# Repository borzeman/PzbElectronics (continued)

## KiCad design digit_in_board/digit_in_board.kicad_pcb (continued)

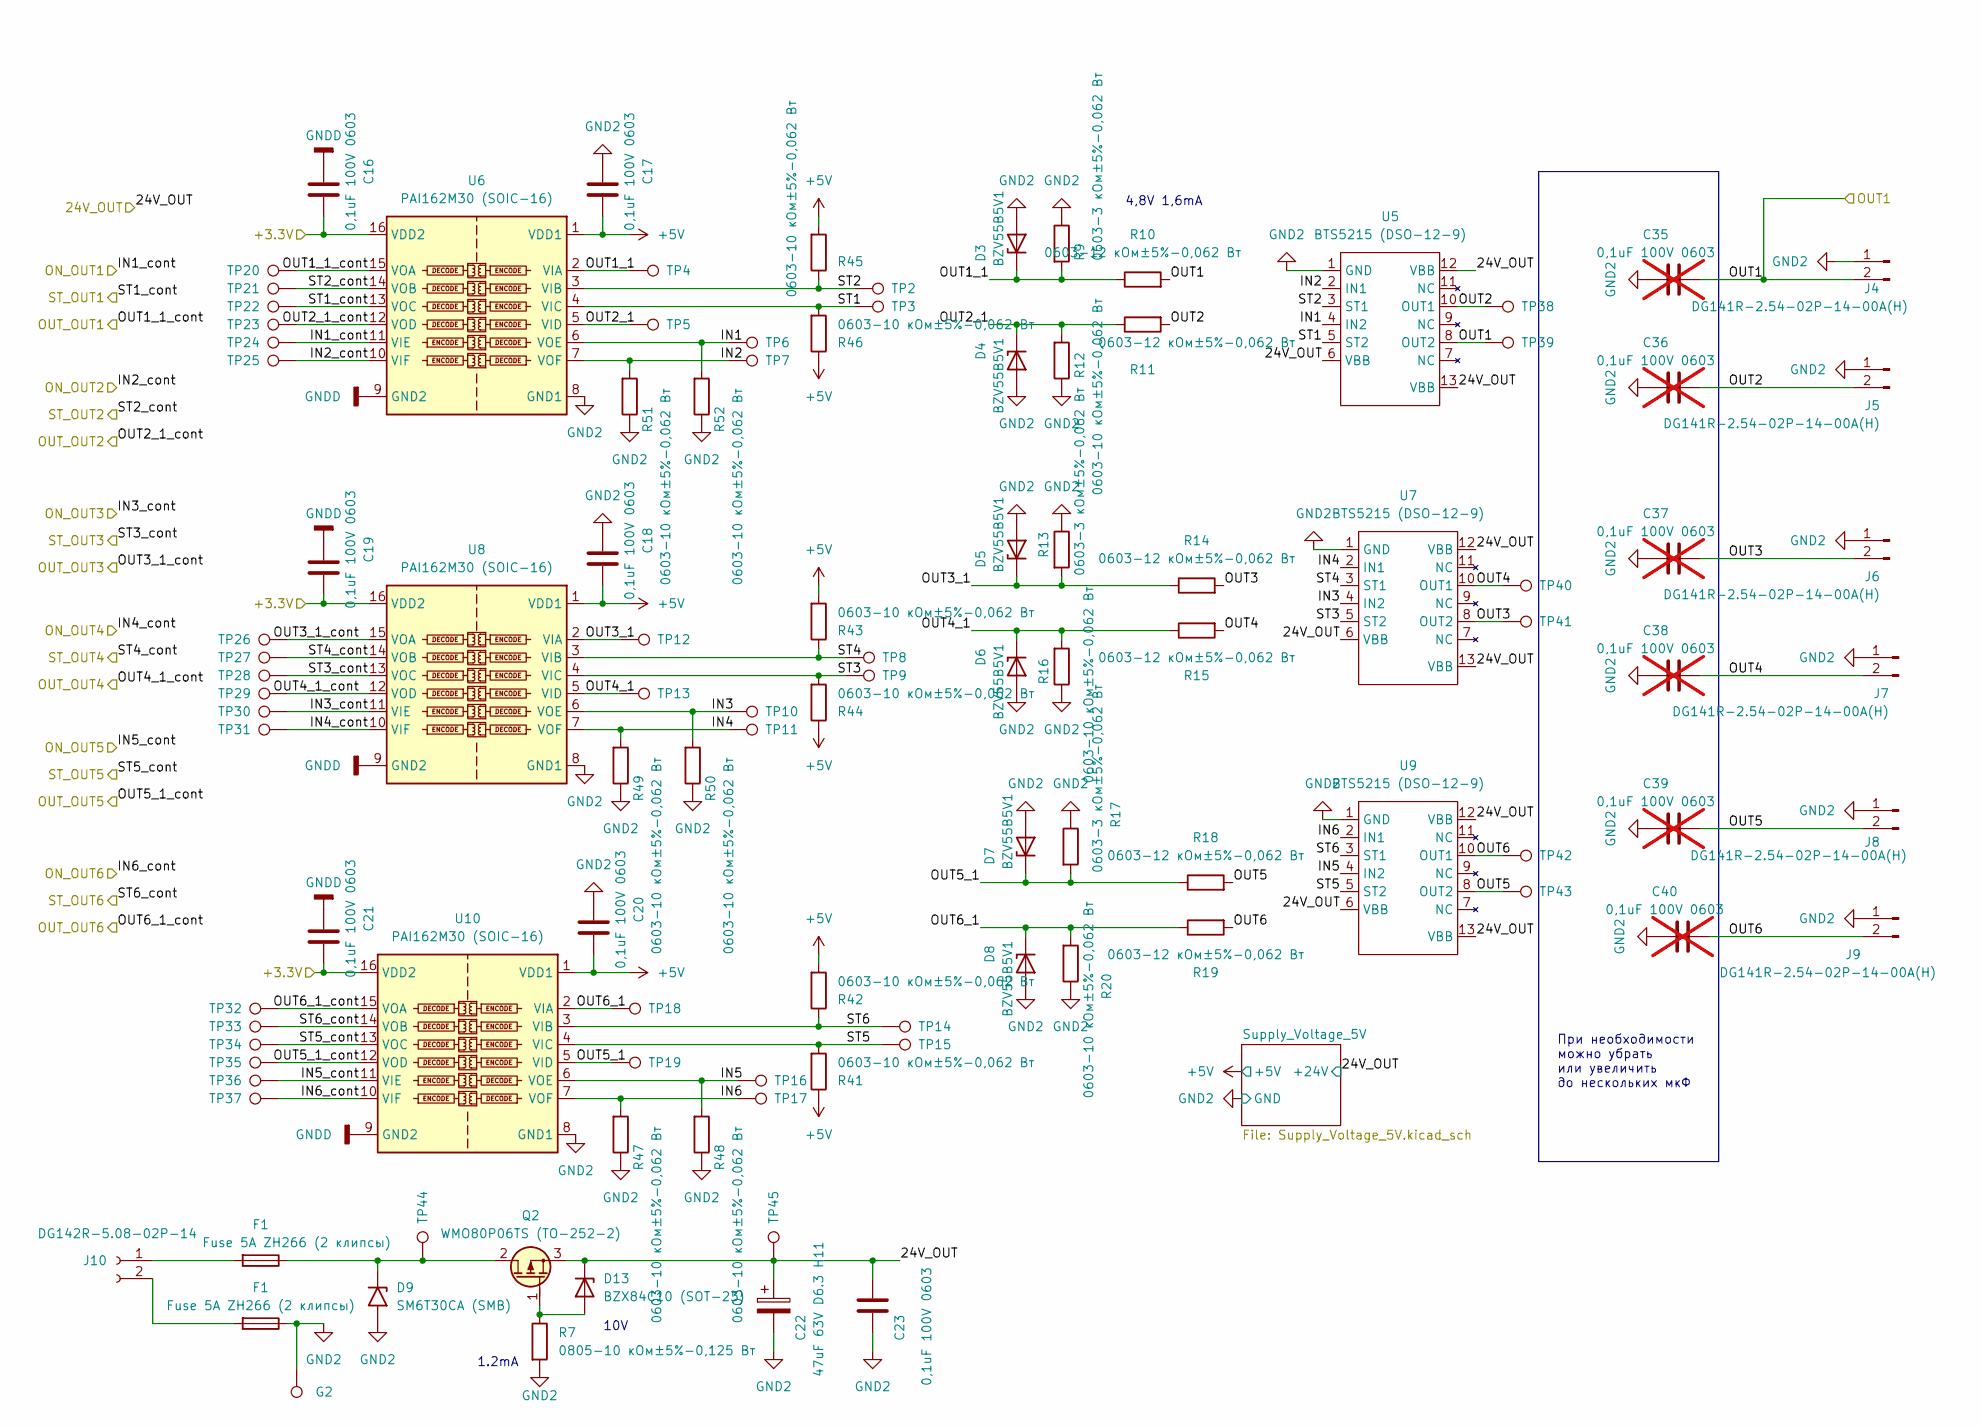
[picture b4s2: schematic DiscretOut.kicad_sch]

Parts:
C16, C17, C18, C19, C20, C21, C23: 0,1uF 100V 0603; C_0603_1608Metric
C22: 47uF 63V D6.3 H11; CP_Radial_D6.3mm_P2.50mm
C35, C36, C37, C38, C39, C40: 0,1uF 100V 0603; C_0603_1608Metric; not fitted
D3, D4, D5, D6, D7, D8: BZV55B5V1; D_MiniMELF
D9: SM6T30СA (SMB); D_SMB
D13: BZX84C10 (SOT-23); SOT-23
F1: Fuse 5A ZH266 (2 клипсы); Fuseholder_100_series_5x20mm_D1,5
G2: TestPoint_D1
J4, J5, J6, J7, J8, J9: DG141R-2.54-02P-14-00A(H); DG141R-02
J10: DG142R-5.08-02P-14
Q2: WMO80P06TS (TO-252-2); TO-252-2
R7: 0805-10 кОм±5%-0,125 Вт; R_0805_2012Metric
R9, R13, R17: 0603-3 кОм±5%-0,062 Вт; R_0603_1608Metric
R10, R11, R14, R15, R18, R19: 0603-12 кОм±5%-0,062 Вт; R_0603_1608Metric
R12, R16, R20, R41, R42, R43, R44, R45, R46, R47, R48, R49, R50, R51, R52: 0603-10 кОм±5%-0,062 Вт; R_0603_1608Metric
TP2, TP3, TP4, TP5, TP6, TP7, TP8, TP9, TP10, TP11, TP12, TP13, TP14, TP15, TP16, TP17, TP18, TP19, TP20, TP21, TP22, TP23, TP24, TP25, TP26, TP27, TP28, TP29, TP30, TP31, TP32, TP33, TP34, TP35, TP36, TP37, TP38, TP39, TP40, TP41, TP42, TP43, TP44, TP45: TestPoint_D1
U5, U7, U9: BTS5215 (DSO-12-9); Infineon_PG-DSO-12-9
U6, U8, U10: PAI162M30 (SOIC-16); SOIC-16_3.9x9.9mm_P1.27mm

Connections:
+3V3: C16.2, C19.2, C21.2, U6.16 (VDD2), U8.16 (VDD2), U10.16 (VDD2); also elsewhere on the board
+5V: C17.2, C18.2, C20.2, R41.1, R42.2, R43.2, R44.1, R45.2, R46.1, U6.1 (VDD1), U8.1 (VDD1), U10.1 (VDD1); also elsewhere on the board
/+24_FT_1: C35.2, J4.2, R10.2, TP39.1, U5.8 (OUT2); also elsewhere on the board
/DiscretOut/IN1: R52.2, TP6.1, U5.4 (IN2), U6.6 (VOE)
/DiscretOut/IN2: R51.2, TP7.1, U5.2 (IN1), U6.7 (VOF)
/DiscretOut/IN3: R50.2, TP10.1, U7.4 (IN2), U8.6 (VOE)
/DiscretOut/IN4: R49.2, TP11.1, U7.2 (IN1), U8.7 (VOF)
/DiscretOut/IN5: R48.2, TP16.1, U9.4 (IN2), U10.6 (VOE)
/DiscretOut/IN6: R47.2, TP17.1, U9.2 (IN1), U10.7 (VOF)
/DiscretOut/OUT1_1: D3.1 (K), R9.2, R10.1, TP4.1, U6.2 (VIA)
/DiscretOut/OUT2: C36.2, J5.2, R11.2, TP38.1, U5.10 (OUT1)
/DiscretOut/OUT2_1: D4.1 (K), R11.1, R12.2, TP5.1, U6.5 (VID)
/DiscretOut/OUT3: C37.2, J6.2, R14.2, TP41.1, U7.8 (OUT2)
/DiscretOut/OUT3_1: D5.1 (K), R13.2, R14.1, TP12.1, U8.2 (VIA)
/DiscretOut/OUT4: C38.2, J7.2, R15.2, TP40.1, U7.10 (OUT1)
/DiscretOut/OUT4_1: D6.1 (K), R15.1, R16.2, TP13.1, U8.5 (VID)
/DiscretOut/OUT5: C39.2, J8.2, R18.2, TP43.1, U9.8 (OUT2)
/DiscretOut/OUT5_1: D7.1 (K), R17.2, R18.1, TP19.1, U10.5 (VID)
/DiscretOut/OUT6: C40.2, J9.2, R19.2, TP42.1, U9.10 (OUT1)
/DiscretOut/OUT6_1: D8.1 (K), R19.1, R20.2, TP18.1, U10.2 (VIA)
/DiscretOut/ST1: R46.2, TP3.1, U5.5 (ST2), U6.4 (VIC)
/DiscretOut/ST2: R45.1, TP2.1, U5.3 (ST1), U6.3 (VIB)
/DiscretOut/ST3: R44.2, TP9.1, U7.5 (ST2), U8.4 (VIC)
/DiscretOut/ST4: R43.1, TP8.1, U7.3 (ST1), U8.3 (VIB)
/DiscretOut/ST5: R41.2, TP15.1, U9.5 (ST2), U10.4 (VIC)
/DiscretOut/ST6: R42.1, TP14.1, U9.3 (ST1), U10.3 (VIB)
/ON_OUT1: TP24.1, U6.11 (VIE); also elsewhere on the board
/ON_OUT2: TP25.1, U6.10 (VIF); also elsewhere on the board
/ON_OUT3: TP30.1, U8.11 (VIE); also elsewhere on the board
/ON_OUT4: TP31.1, U8.10 (VIF); also elsewhere on the board
/ON_OUT5: TP36.1, U10.11 (VIE); also elsewhere on the board
/ON_OUT6: TP37.1, U10.10 (VIF); also elsewhere on the board
/OUT1_1_cont: TP20.1, U6.15 (VOA); also elsewhere on the board
/OUT2_1_cont: TP23.1, U6.12 (VOD); also elsewhere on the board
/OUT3_1_cont: TP26.1, U8.15 (VOA); also elsewhere on the board
/OUT4_1_cont: TP29.1, U8.12 (VOD); also elsewhere on the board
/OUT5_1_cont: TP35.1, U10.12 (VOD); also elsewhere on the board
/OUT6_1_cont: TP33.1, U10.14 (VOB); also elsewhere on the board
/ST1_cont: TP22.1, U6.13 (VOC); also elsewhere on the board
/ST2_cont: TP21.1, U6.14 (VOB); also elsewhere on the board
/ST3_cont: TP28.1, U8.13 (VOC); also elsewhere on the board
/ST4_cont: TP27.1, U8.14 (VOB); also elsewhere on the board
/ST5_cont: TP34.1, U10.13 (VOC); also elsewhere on the board
/ST6_cont: TP32.1, U10.15 (VOA); also elsewhere on the board

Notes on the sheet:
При необходимости можно убрать или увеличить до нескольких мкФ
4,8V 1,6mA
10V
1.2mA

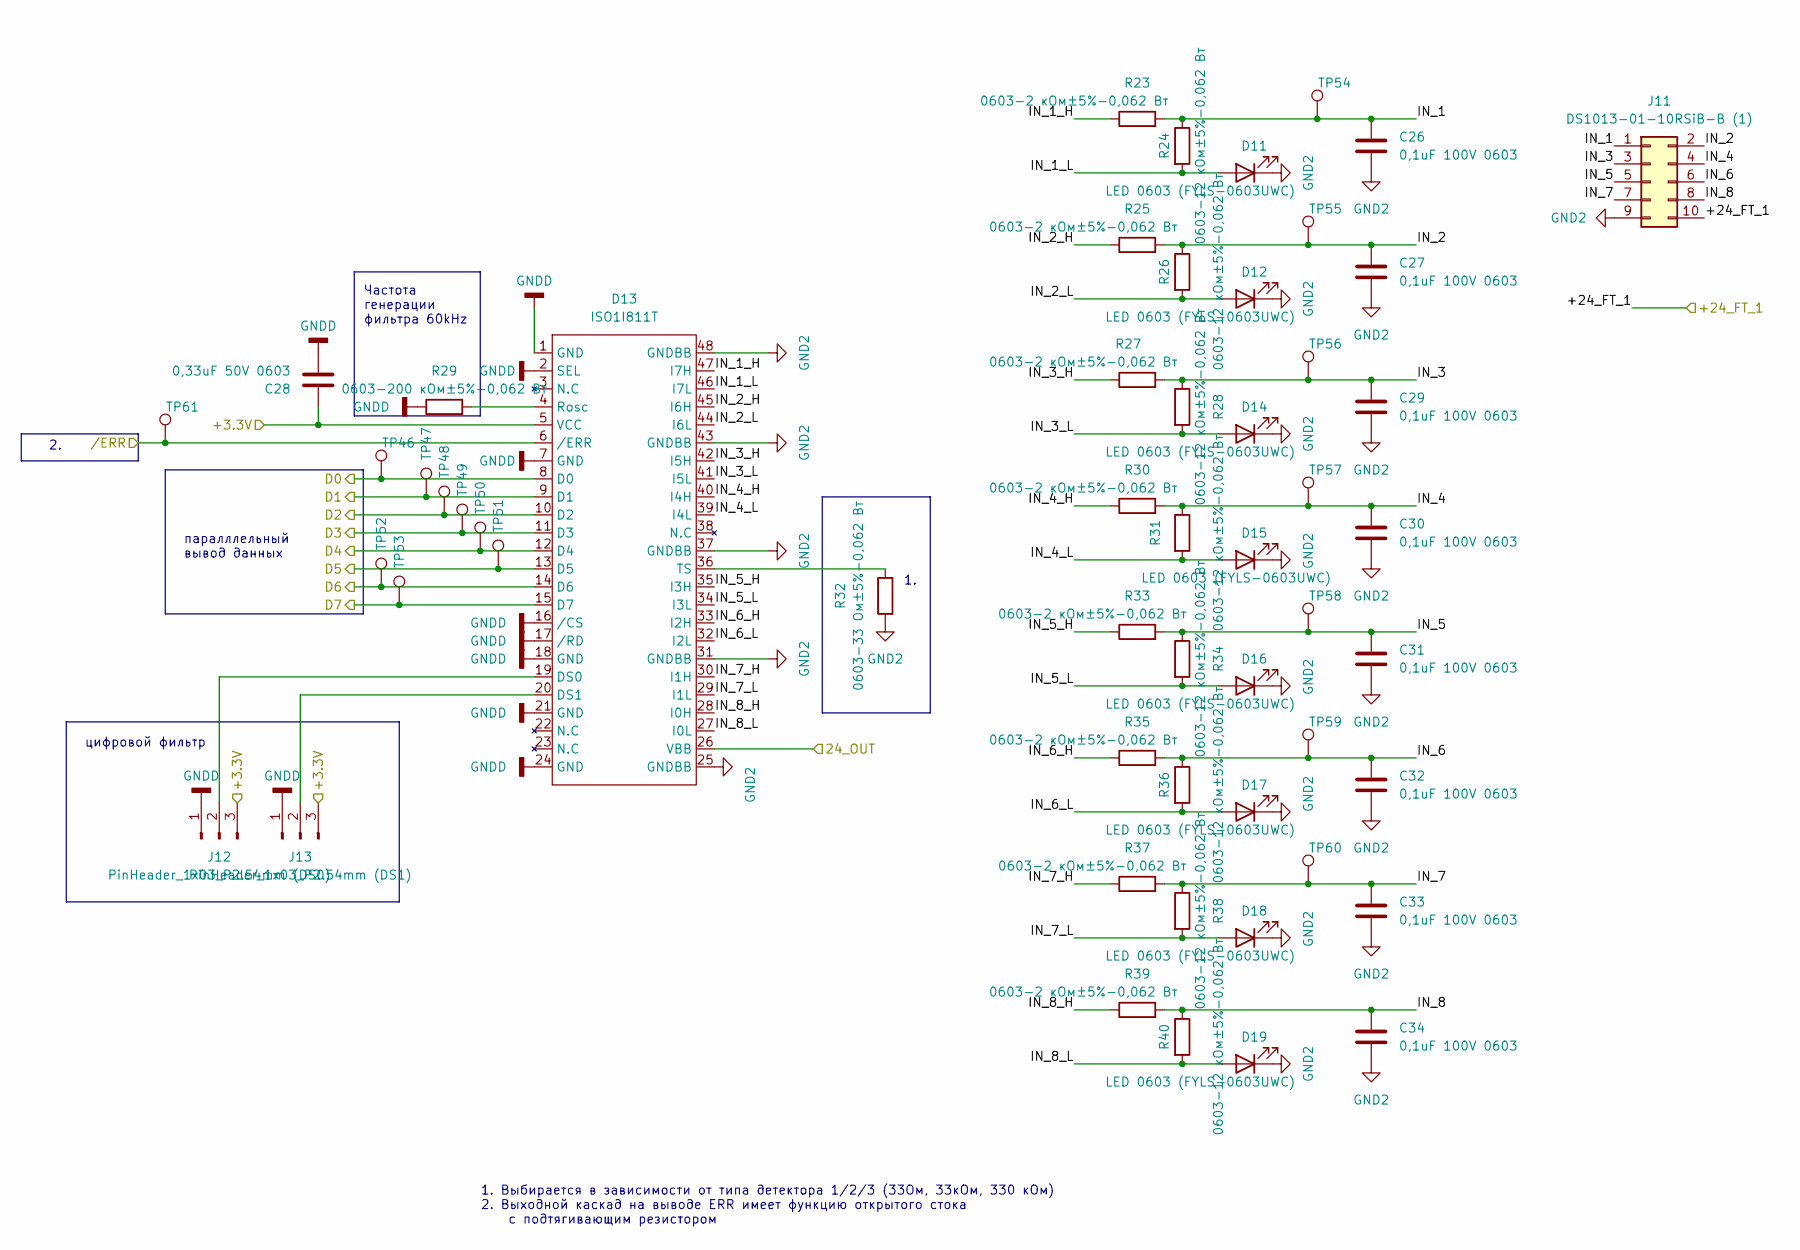
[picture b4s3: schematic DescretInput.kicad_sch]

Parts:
C26, C27, C29, C30, C31, C32, C33, C34: 0,1uF 100V 0603; C_0603_1608Metric
C28: 0,33uF 50V 0603; C_0603_1608Metric_Pad1.08x0.95mm_HandSolder
D11, D12, D14, D15, D16, D17, D18, D19: LED 0603 (FYLS-0603UWC); LED_0603_1608Metric_Pad1.05x0.95mm_HandSolder
D13: ISO1I811T; TSSOP-48_6.1x12.5mm_P0.5mm
J11: DS1013-01-10RSiB-B (1); IDC-Header_2x05_P2.54mm_Horizontal
J12: PinHeader_1x03_P2.54mm (DS0); PinHeader_1x03_P2.54mm_Vertical
J13: PinHeader_1x03_P2.54mm (DS1); PinHeader_1x03_P2.54mm_Vertical
R23, R25, R27, R30, R33, R35, R37, R39: 0603-2 кОм±5%-0,062 Вт; R_0603_1608Metric
R24, R26, R28, R31, R34, R36, R38, R40: 0603-12 кОм±5%-0,062 Вт; R_0603_1608Metric
R29: 0603-200 кОм±5%-0,062 Вт; R_0603_1608Metric
R32: 0603-33 Ом±5%-0,062 Вт; R_0603_1608Metric
TP46, TP47, TP48, TP49, TP50, TP51, TP52, TP53, TP54, TP55, TP56, TP57, TP58, TP59, TP60, TP61: TestPoint_D1

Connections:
+3V3: C28.1, D13.5 (VCC), J12.3, J13.3; also elsewhere on the board
/+24_FT_1: J11.10; also elsewhere on the board
/D0: D13.8 (D0), TP46.1; also elsewhere on the board
/D1: D13.9 (D1), TP47.1; also elsewhere on the board
/D2: D13.10 (D2), TP48.1; also elsewhere on the board
/D3: D13.11 (D3), TP49.1; also elsewhere on the board
/D4: D13.12 (D4), TP50.1; also elsewhere on the board
/D5: D13.13 (D5), TP51.1; also elsewhere on the board
/D6: D13.14 (D6), TP52.1; also elsewhere on the board
/D7: D13.15 (D7), TP53.1; also elsewhere on the board
/Descret Input/IN_1: C26.1, J11.1, R23.2, R24.1, TP54.1
/Descret Input/IN_1_H: D13.47 (I7H), R23.1
/Descret Input/IN_1_L: D11.2 (A), D13.46 (I7L), R24.2
/Descret Input/IN_2: C27.1, J11.2, R25.2, R26.1, TP55.1
/Descret Input/IN_2_H: D13.45 (I6H), R25.1
/Descret Input/IN_2_L: D12.2 (A), D13.44 (I6L), R26.2
/Descret Input/IN_3: C29.1, J11.3, R27.2, R28.1, TP56.1
/Descret Input/IN_3_H: D13.42 (I5H), R27.1
/Descret Input/IN_3_L: D13.41 (I5L), D14.2 (A), R28.2
/Descret Input/IN_4: C30.1, J11.4, R30.2, R31.1, TP57.1
/Descret Input/IN_4_H: D13.40 (I4H), R30.1
/Descret Input/IN_4_L: D13.39 (I4L), D15.2 (A), R31.2
/Descret Input/IN_5: C31.1, J11.5, R33.2, R34.1, TP58.1
/Descret Input/IN_5_H: D13.35 (I3H), R33.1
/Descret Input/IN_5_L: D13.34 (I3L), D16.2 (A), R34.2
/Descret Input/IN_6: C32.1, J11.6, R35.2, R36.1, TP59.1
/Descret Input/IN_6_H: D13.33 (I2H), R35.1
/Descret Input/IN_6_L: D13.32 (I2L), D17.2 (A), R36.2
/Descret Input/IN_7: C33.1, J11.7, R37.2, R38.1, TP60.1
/Descret Input/IN_7_H: D13.30 (I1H), R37.1
/Descret Input/IN_7_L: D13.29 (I1L), D18.2 (A), R38.2
/Descret Input/IN_8: C34.1, J11.8, R39.2, R40.1
/Descret Input/IN_8_H: D13.28 (I0H), R39.1
/Descret Input/IN_8_L: D13.27 (I0L), D19.2 (A), R40.2
/ERR: D13.6 (/ERR), TP61.1; also elsewhere on the board
unnamed: D13.19 (DS0), J12.2
unnamed: D13.20 (DS1), J13.2
unnamed: D13.4 (Rosc), R29.2
unnamed: D13.36 (TS), R32.2

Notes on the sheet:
1. Выбирается в зависимости от типа детектора 1/2/3 (33Ом, 33кОм, 330 кОм) 2. Выходной каскад на выводе ERR имеет функцию открытого стока с подтягивающим резистором
паралллельный вывод данных
цифровой фильтр
Частота генерации фильтра 60kHz

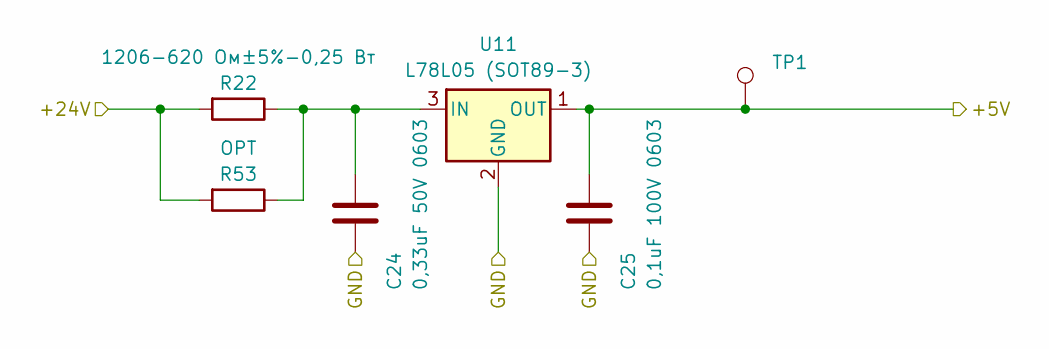
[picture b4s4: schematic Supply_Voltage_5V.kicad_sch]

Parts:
C24: 0,33uF 50V 0603; C_0603_1608Metric_Pad1.08x0.95mm_HandSolder
C25: 0,1uF 100V 0603; C_0603_1608Metric
R22: 1206-620 Ом±5%-0,25 Вт; R_1206_3216Metric_Pad1.42x1.75mm_HandSolder
R53: OPT; R_1206_3216Metric_Pad1.42x1.75mm_HandSolder
TP1: TestPoint_D1
U11: L78L05 (SOT89-3); SOT-89-3

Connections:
+5V: C25.1, TP1.1, U11.1 (OUT); also elsewhere on the board
unnamed: C24.1, R22.1, R53.1, U11.3 (IN)

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
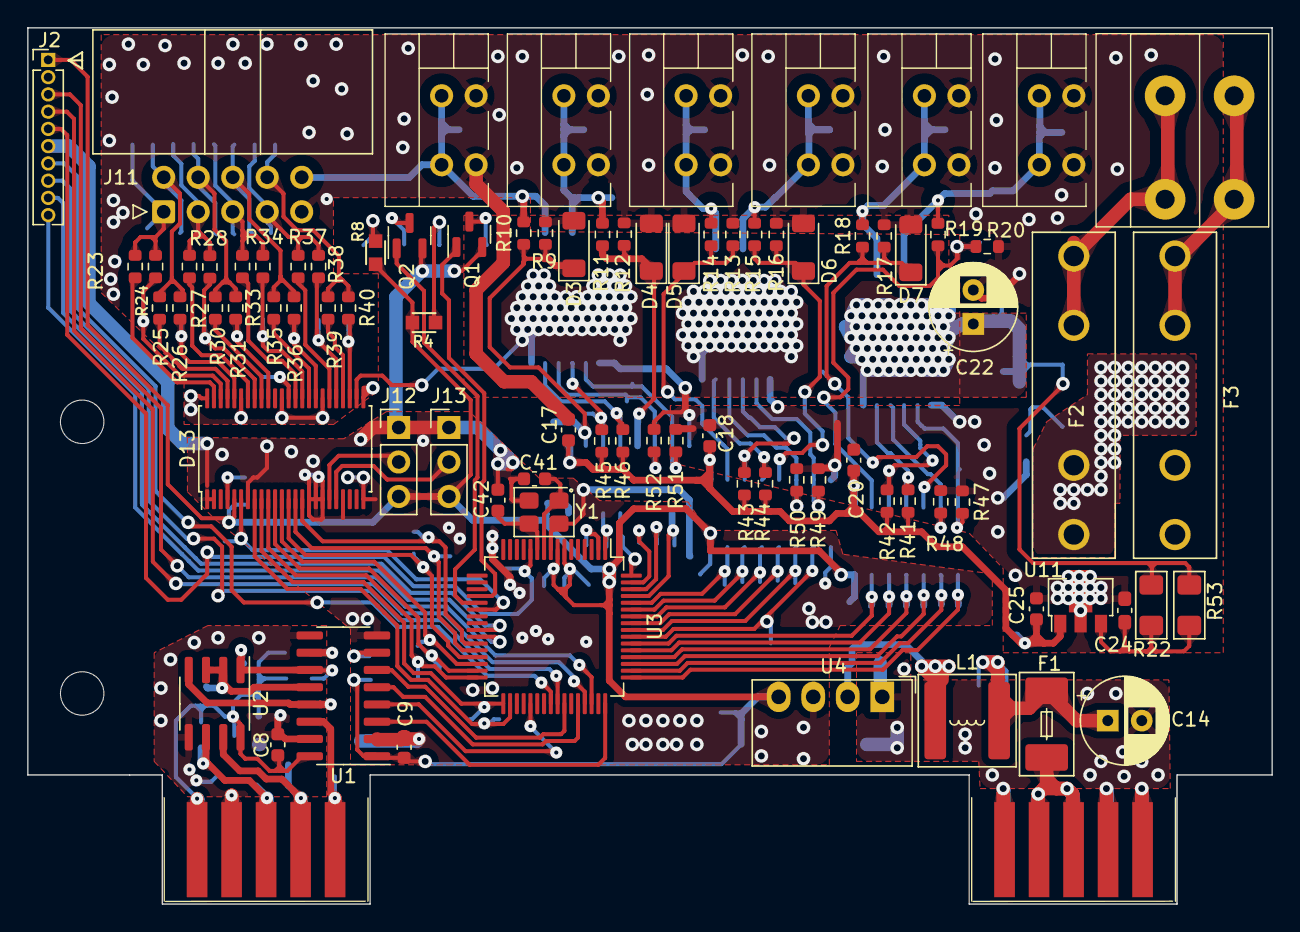
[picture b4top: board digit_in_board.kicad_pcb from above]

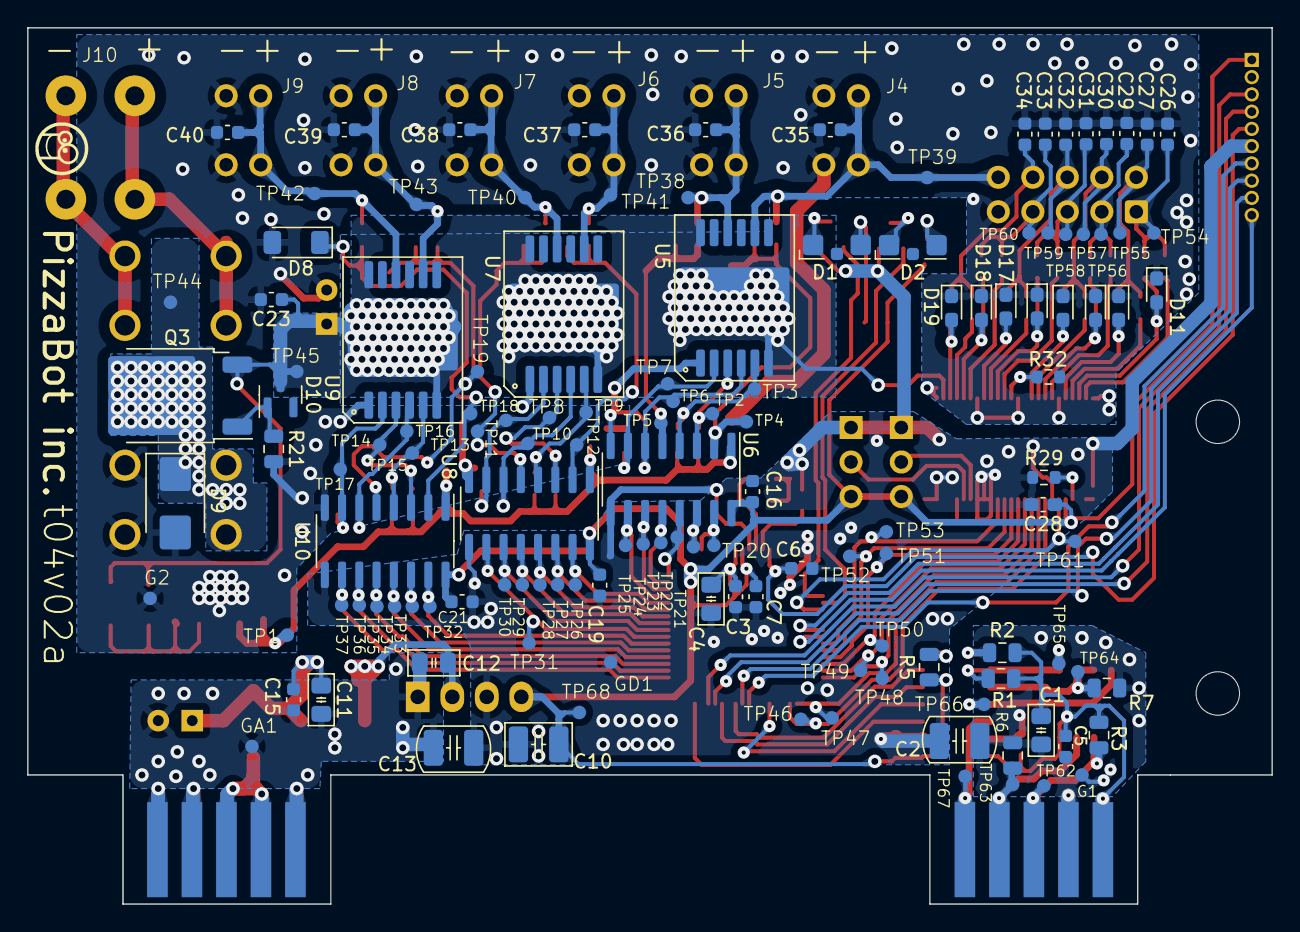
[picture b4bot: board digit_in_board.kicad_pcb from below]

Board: 2 copper layers, 91.6 x 64.5 mm, 220 parts (132 on the bottom side), 122 nets.

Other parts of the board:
D10: BZX84C10 (SOT-23); SOT-23
F2, F3: Fuse 5A ZH266 (2 клипсы); Fuseholder_100_series_5x20mm_D1,5
Q3: WMO80P06TS (TO-252-2); TO-252-2
R21: 0805-10 кОм±5%-0,125 Вт; R_0805_2012Metric

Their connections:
unnamed: D10.1 (A), Q3.1 (G), R21.1

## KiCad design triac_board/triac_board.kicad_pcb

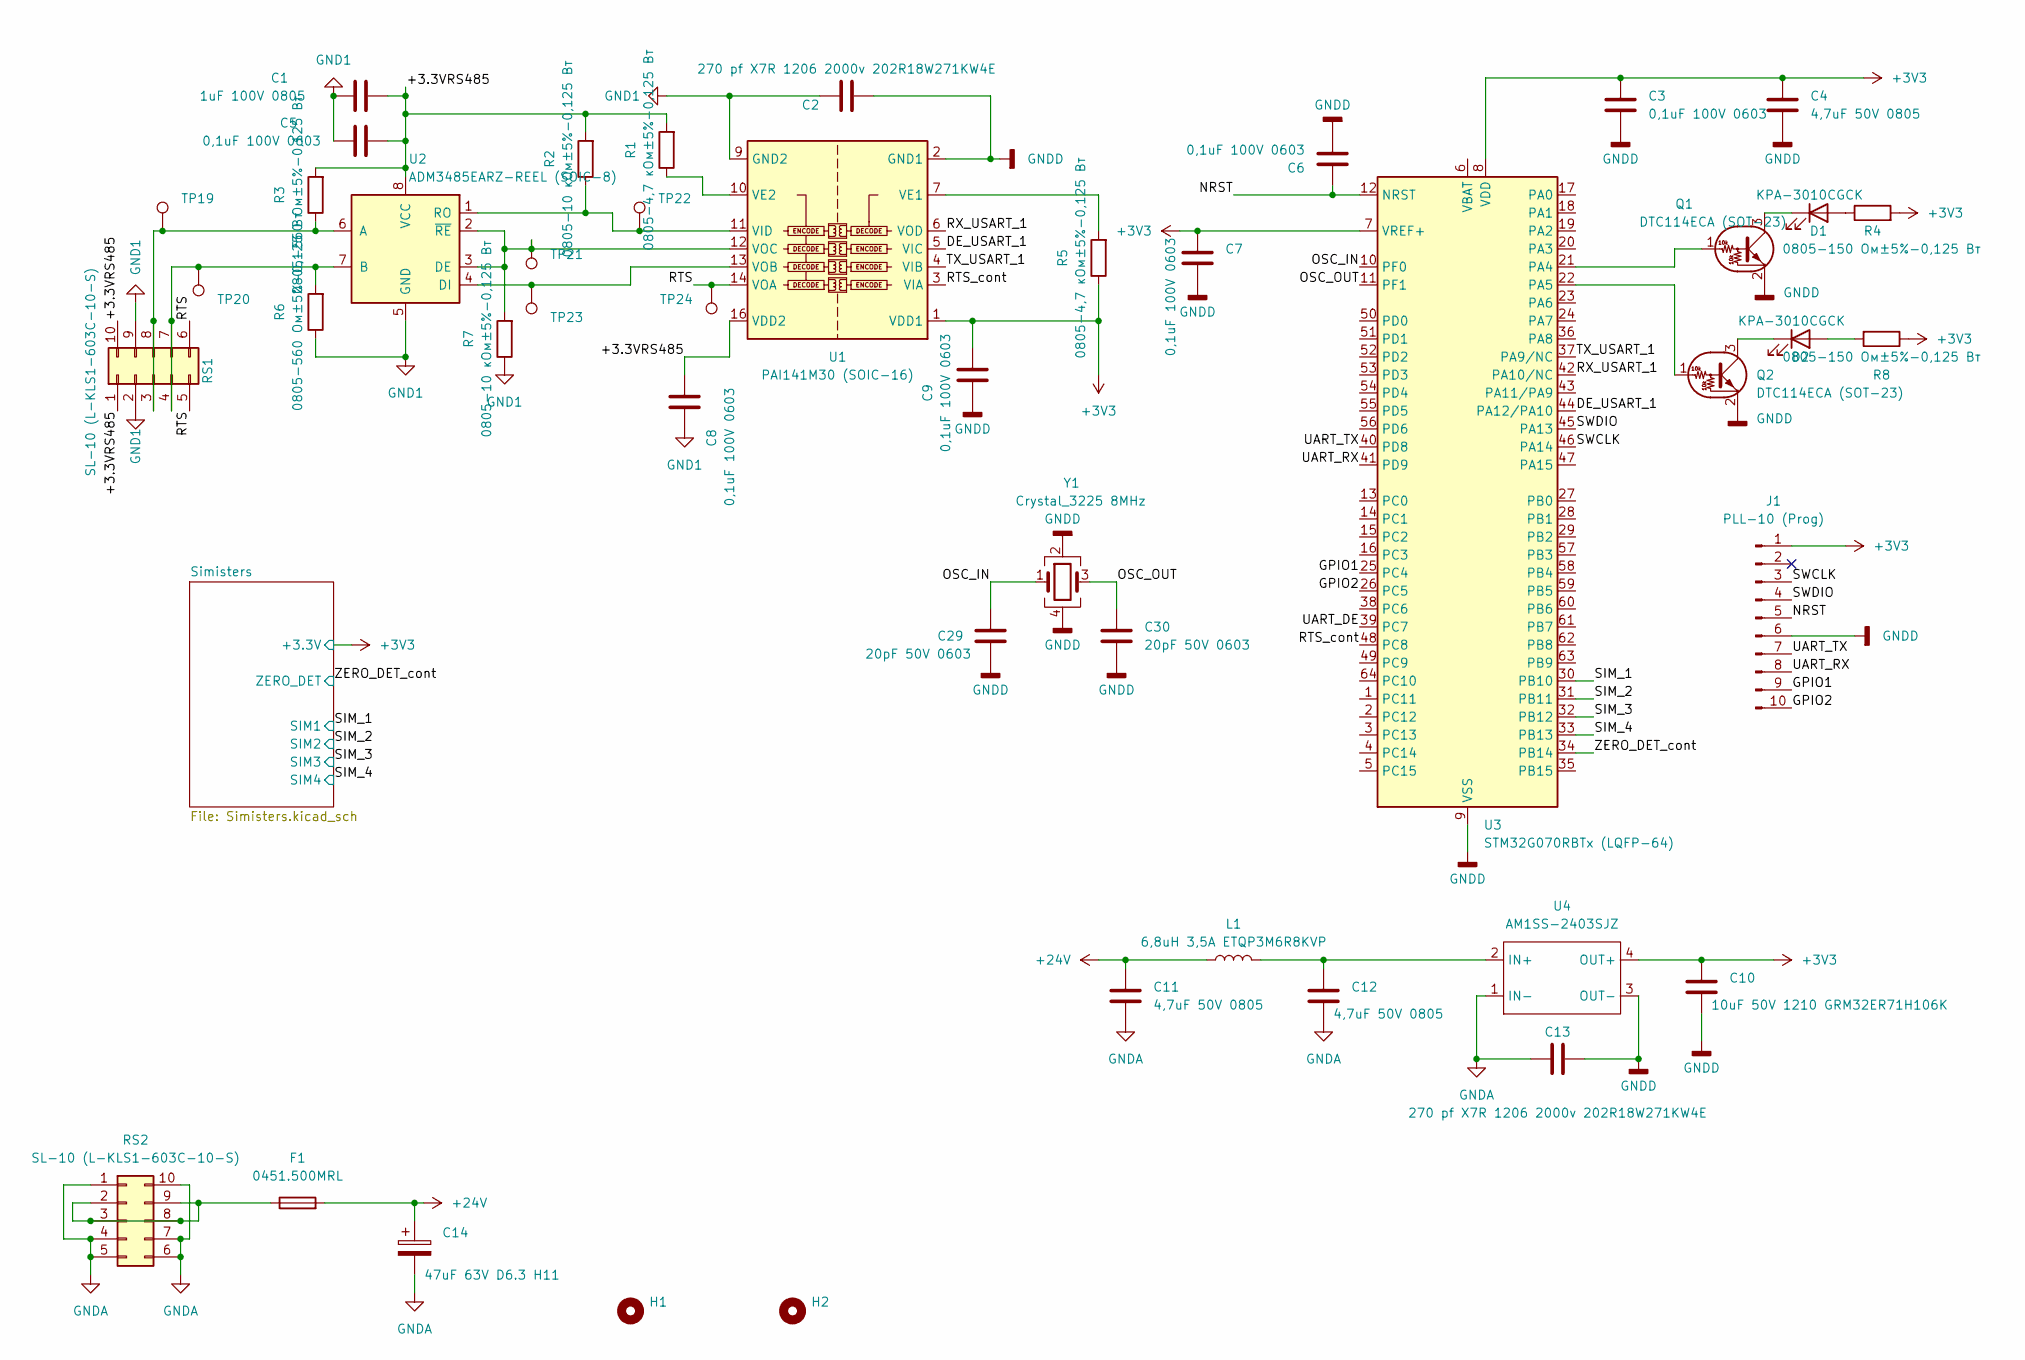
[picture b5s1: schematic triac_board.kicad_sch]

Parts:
C1: 1uF 100V 0805; C_0805_2012Metric_Pad1.18x1.45mm_HandSolder
C2, C13: 270 pf X7R 1206 2000v 202R18W271KW4E; C_1210_3225Metric_Pad1.42x2.65mm
C3, C5, C6, C7, C8, C9: 0,1uF 100V 0603; C_0603_1608Metric
C4, C11, C12: 4,7uF 50V 0805; C_0805_2012Metric_Pad1.18x1.45mm_HandSolder
C10: 10uF 50V 1210 GRM32ER71H106K; C_1210_3225Metric_Pad1.42x2.65mm_HandSolder
C14: 47uF 63V D6.3 H11; CP_Radial_D6.3mm_P2.50mm
C29, C30: 20pF 50V 0603; C_0603_1608Metric
D1, D2: KPA-3010CGCK; LED_Kingbright_KPA-3010_3x2x1mm
F1: 0451.500MRL; Fuse_Littelfuse-NANO2-451_453
H1, H2: MountingHole; MountingHole_3.2mm_M3
J1: PLL-10 (Prog); PinHeader_1x10_P1.27mm_Vertical
L1: 6,8uH 3,5A ETQP3M6R8KVP; L_Bourns-SRN6028
Q1, Q2: DTC114ECA (SOT-23); SOT-23
R1, R5: 0805-4,7 кОм±5%-0,125 Вт; R_0805_2012Metric
R2, R7: 0805-10 кОм±5%-0,125 Вт; R_0805_2012Metric
R3, R6: 0805-560 Ом±5%-0,125 Вт; R_0805_2012Metric
R4, R8: 0805-150 Ом±5%-0,125 Вт; R_0805_2012Metric
RS1, RS2: SL-10 (L-KLS1-603C-10-S); Edge_Conn_KLS1-603-10
TP19, TP20, TP21, TP22, TP23, TP24: TestPoint; TestPoint_D1
U1: PAI141M30 (SOIC-16); SOIC-16_3.9x9.9mm_P1.27mm
U2: ADM3485EARZ-REEL (SOIC-8); SOIC-8_3.9x4.9mm_P1.27mm
U3: STM32G070RBTx (LQFP-64); LQFP-64_10x10mm_P0.5mm
U4: AM1SS-2403SJZ; Converter_DCDC_Murata_MEE3SxxxxSC_THT
Y1: Crystal_3225 8MHz; Crystal_SMD_3225-4Pin_3.2x2.5mm

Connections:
+3V3: C3.1, C4.1, C7.1, C9.2, C10.1, J1.1, R4.2, R5.1, R8.1, U1.1 (VDD1), U3.7 (VREF+), U3.8 (VDD), U4.4 (OUT+); also elsewhere on the board
+24V: C11.1, C14.1, F1.2, L1.1
/+3.3VRS485: C1.2, C5.2, C8.2, R1.2, R2.2, R3.2, RS1.1, RS1.10, U1.16 (VDD2), U2.8 (VCC)
/DE_USART_1: U1.5 (VIC), U3.44 (PA12/PA10)
/GPIO1: J1.9, U3.25 (PC4)
/GPIO2: J1.10, U3.26 (PC5)
/NRST: C6.1, J1.5, U3.12 (NRST)
/OSC_IN: C29.1, U3.10 (PF0), Y1.1
/OSC_OUT: C30.1, U3.11 (PF1), Y1.3
/RTS: RS1.5, RS1.6, TP24.1, U1.14 (VOA)
/RTS_cont: U1.3 (VIA), U3.48 (PC8)
/RX_USART_1: U1.6 (VOD), U3.42 (PA10/NC)
/SIM_1: U3.30 (PB10); also elsewhere on the board
/SIM_2: U3.31 (PB11); also elsewhere on the board
/SIM_3: U3.32 (PB12); also elsewhere on the board
/SIM_4: U3.33 (PB13); also elsewhere on the board
/SWCLK: J1.3, U3.46 (PA14)
/SWDIO: J1.4, U3.45 (PA13)
/TX_USART_1: U1.4 (VIB), U3.37 (PA9/NC)
/UART_DE: U3.39 (PC7)
/UART_RX: J1.8, U3.41 (PD9)
/UART_TX: J1.7, U3.40 (PD8)
/ZERO_DET_cont: U3.34 (PB14); also elsewhere on the board
GND1: C1.1, C2.1, C5.1, C8.1, R6.1, R7.1, RS1.2, RS1.9, U1.9 (GND2), U1.15 (GND2), U2.5 (GND)
GNDA: C11.2, C12.2, C13.1, C14.2, RS2.1, RS2.4, RS2.5, RS2.6, RS2.7, RS2.10, U4.1 (IN-)
GNDD: C2.2, C3.2, C4.2, C6.2, C7.2, C9.1, C10.2, C13.2, C29.2, C30.2, J1.6, Q1.2 (E), Q2.2 (E), U1.2 (GND1), U1.8 (GND1), U3.9 (VSS), U4.3 (OUT-), Y1.2, Y1.4; also elsewhere on the board
unnamed: D1.2 (A), R4.1
unnamed: D1.1 (K), Q1.3 (C)
unnamed: D2.2 (A), R8.2
unnamed: D2.1 (K), Q2.3 (C)
unnamed: Q1.1 (B), U3.21 (PA4)
unnamed: Q2.1 (B), U3.22 (PA5)
unnamed: R3.1, RS1.3, RS1.8, TP19.1, U2.6 (A)
unnamed: R6.2, RS1.4, RS1.7, TP20.1, U2.7 (B)
unnamed: F1.1, RS2.2, RS2.3, RS2.8, RS2.9
unnamed: R5.2, U1.7 (VE1)
unnamed: R1.1, U1.10 (VE2)
unnamed: R2.1, TP22.1, U1.11 (VID), U2.1 (RO)
unnamed: TP23.1, U1.13 (VOB), U2.4 (DI)
unnamed: R7.2, TP21.1, U1.12 (VOC), U2.2 (~RE), U2.3 (DE)
unnamed: C12.1, L1.2, U4.2 (IN+)

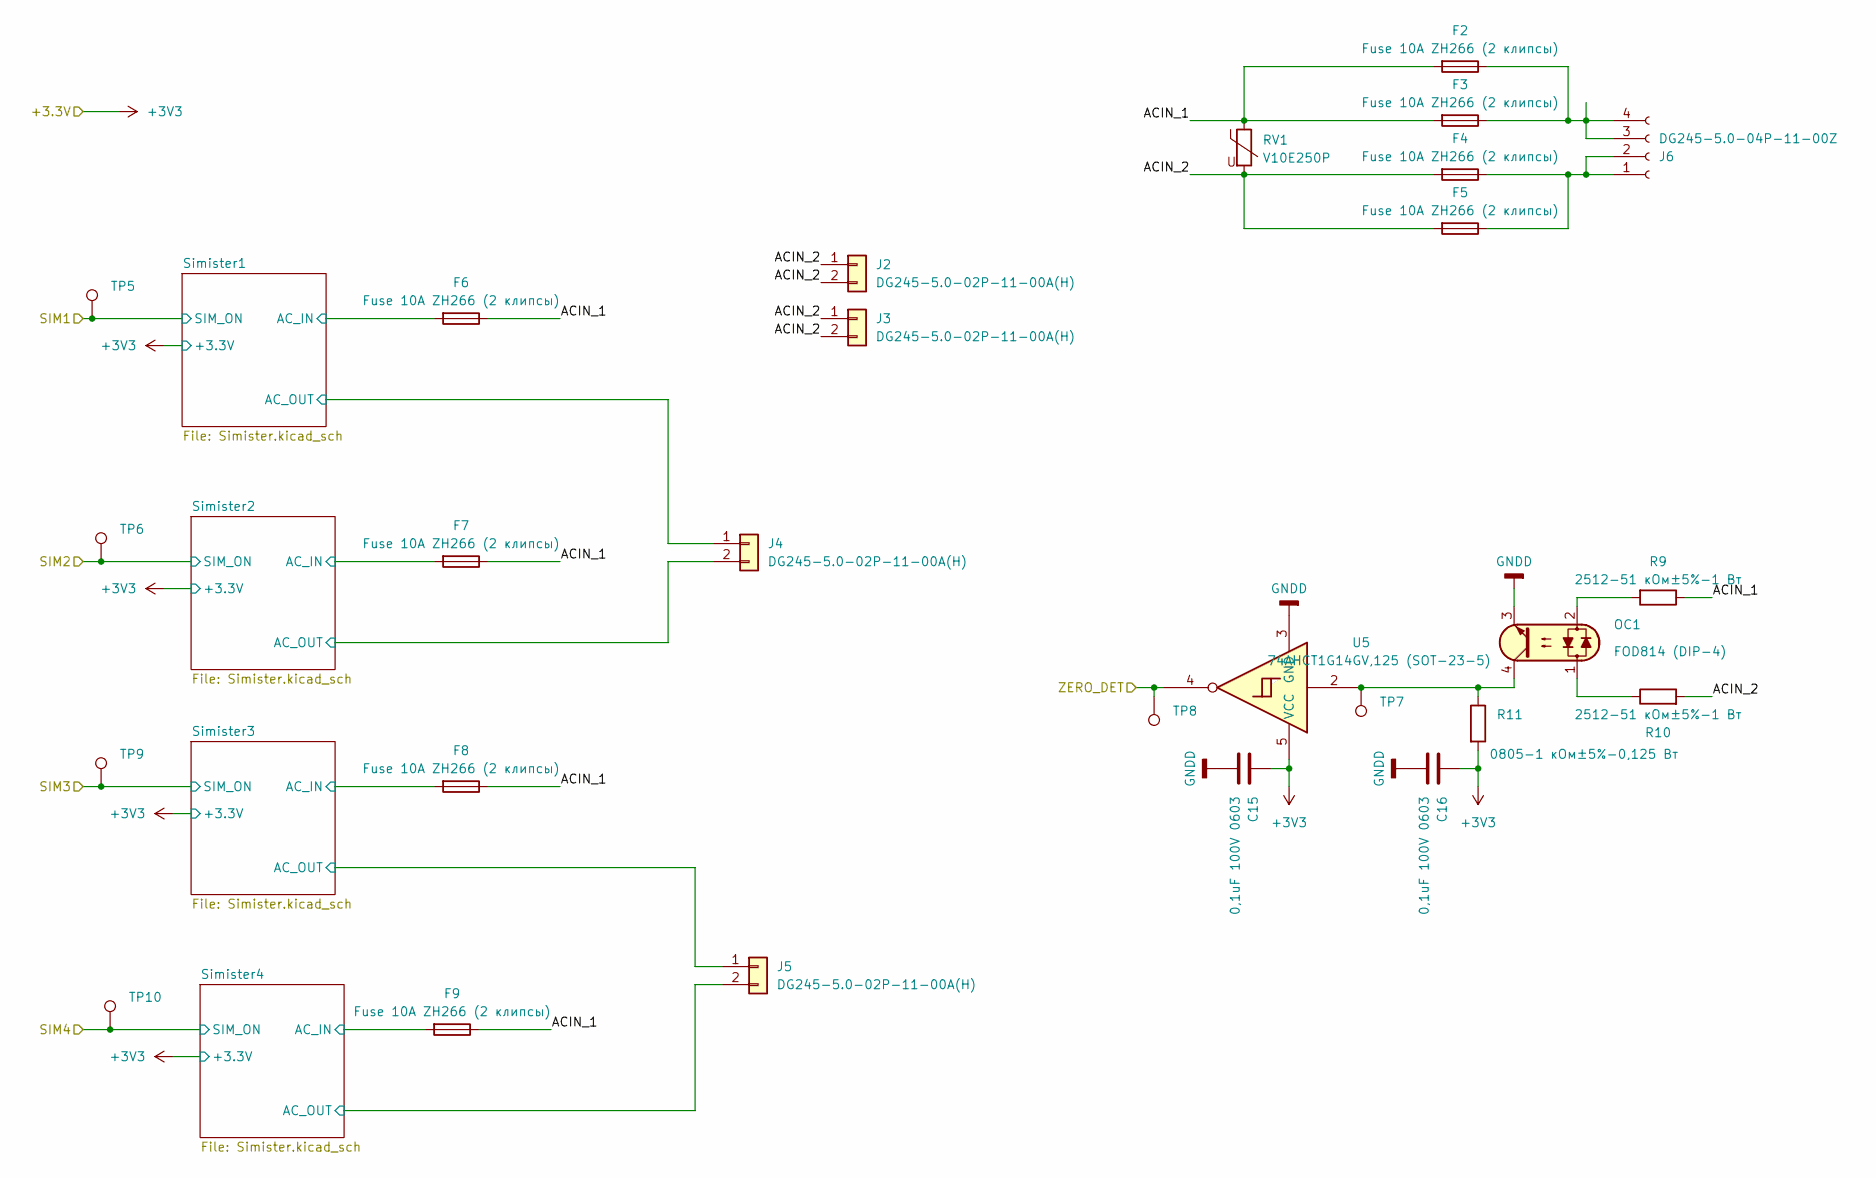
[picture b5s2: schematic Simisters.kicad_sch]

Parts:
C15, C16: 0,1uF 100V 0603; C_0603_1608Metric
F2, F3, F4, F5, F6, F7, F8, F9: Fuse 10A ZH266 (2 клипсы); Fuseholder_100_series_5x20mm_D1,5
J2, J3, J4, J5: DG245-5.0-02P-11-00A(H); DG245-5.0-02P
J6: DG245-5.0-04P-11-00Z; DG245-5.0-04P
OC1: FOD814 (DIP-4); DIP-4_W7.62mm_LongPads
R9, R10: 2512-51 кОм±5%-1 Вт; R_2512_6332Metric
R11: 0805-1 кОм±5%-0,125 Вт; R_0805_2012Metric_Pad1.20x1.40mm_HandSolder
RV1: V10E250P; RV_Disc_D12mm_W5.8mm_P7.5mm
TP5, TP6, TP7, TP8, TP9, TP10: TestPoint; TestPoint_D1
U5: 74AHCT1G14GV,125 (SOT-23-5); SOT-23-5

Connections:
+3V3: C15.1, C16.1, R11.2, U5.5 (VCC); also elsewhere on the board
/SIM_1: TP5.1; also elsewhere on the board
/SIM_2: TP6.1; also elsewhere on the board
/SIM_3: TP9.1; also elsewhere on the board
/SIM_4: TP10.1; also elsewhere on the board
/Simisters/ACIN_1: F2.2, F3.2, F6.1, F7.1, F8.1, F9.1, R9.1, RV1.1
/Simisters/ACIN_2: F4.2, F5.2, J2.1, J2.2, J3.1, J3.2, R10.2, RV1.2
/Simisters/Simister1/AC_IN: F6.2; also elsewhere on the board
/Simisters/Simister1/AC_OUT: J4.1; also elsewhere on the board
/Simisters/Simister2/AC_IN: F7.2; also elsewhere on the board
/Simisters/Simister2/AC_OUT: J4.2; also elsewhere on the board
/Simisters/Simister3/AC_IN: F8.2; also elsewhere on the board
/Simisters/Simister3/AC_OUT: J5.1; also elsewhere on the board
/Simisters/Simister4/AC_IN: F9.2; also elsewhere on the board
/Simisters/Simister4/AC_OUT: J5.2; also elsewhere on the board
/ZERO_DET_cont: TP8.1, U5.4; also elsewhere on the board
GNDD: C15.2, C16.2, OC1.3, U5.3 (GND); also elsewhere on the board
unnamed: F4.1, F5.1, J6.1, J6.2
unnamed: F2.1, F3.1, J6.3, J6.4
unnamed: OC1.1, R10.1
unnamed: OC1.2, R9.2
unnamed: OC1.4, R11.1, TP7.1, U5.2

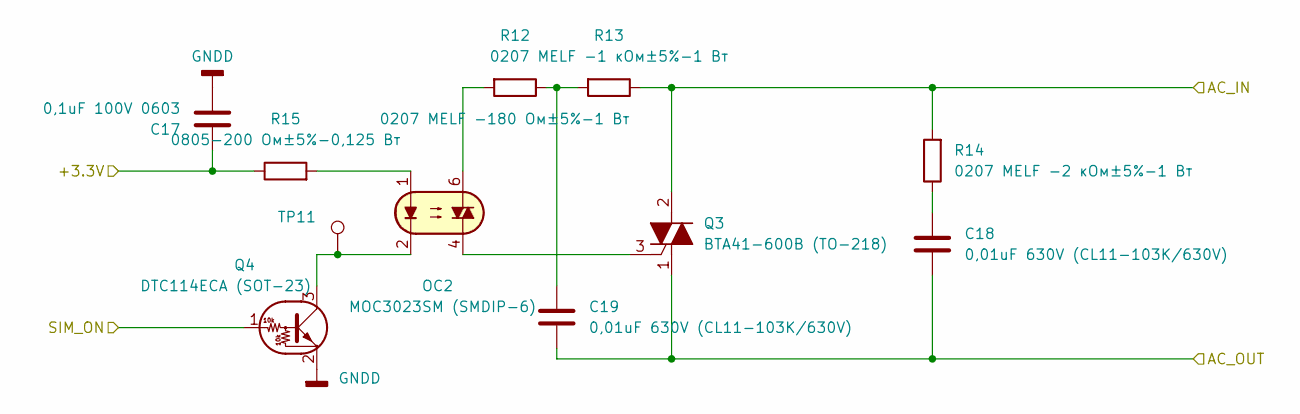
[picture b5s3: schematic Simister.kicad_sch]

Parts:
C17: 0,1uF 100V 0603; C_0603_1608Metric
C18, C19: 0,01uF 630V (CL11-103K/630V); C_Rect_L7.0mm_W4.5mm_P5.00mm
OC2: MOC3023SM (SMDIP-6); SMDIP-6_W9.53mm
Q3: BTA41-600B (TO-218); TO-218-3_Horizontal_TabDown
Q4: DTC114ECA (SOT-23); SOT-23
R12: 0207 MELF -180 Ом±5%-1 Вт; R_MELF_MMB-0207
R13: 0207 MELF -1 кОм±5%-1 Вт; R_MELF_MMB-0207
R14: 0207 MELF -2 кОм±5%-1 Вт; R_MELF_MMB-0207
R15: 0805-200 Ом±5%-0,125 Вт; R_0805_2012Metric
TP11: TestPoint; TestPoint_D1

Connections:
+3V3: C17.1, R15.1; also elsewhere on the board
/SIM_1: Q4.1 (B); also elsewhere on the board
/Simisters/Simister1/AC_IN: Q3.2 (A2), R13.1, R14.2; also elsewhere on the board
/Simisters/Simister1/AC_OUT: C18.2, C19.2, Q3.1 (A1); also elsewhere on the board
GNDD: C17.2, Q4.2 (E); also elsewhere on the board
unnamed: C18.1, R14.1
unnamed: C19.1, R12.1, R13.2
unnamed: OC2.1, R15.2
unnamed: OC2.6, R12.2
unnamed: OC2.4, Q3.3 (G)
unnamed: OC2.2, Q4.3 (C), TP11.1

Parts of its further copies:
C20, C23, C26: 0,1uF 100V 0603; C_0603_1608Metric
C21, C22, C24, C25, C27, C28: 0,01uF 630V (CL11-103K/630V); C_Rect_L7.0mm_W4.5mm_P5.00mm
OC3, OC4, OC5: MOC3023SM (SMDIP-6); SMDIP-6_W9.53mm
Q5, Q7, Q9: BTA41-600B (TO-218); TO-218-3_Horizontal_TabDown
Q6, Q8, Q10: DTC114ECA (SOT-23); SOT-23
R16, R20, R24: 0207 MELF -180 Ом±5%-1 Вт; R_MELF_MMB-0207
R17, R21, R25: 0207 MELF -1 кОм±5%-1 Вт; R_MELF_MMB-0207
R18, R22, R26: 0207 MELF -2 кОм±5%-1 Вт; R_MELF_MMB-0207
R19, R23, R27: 0805-200 Ом±5%-0,125 Вт; R_0805_2012Metric
TP13, TP15, TP17: TestPoint; TestPoint_D1

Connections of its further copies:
+3V3: C20.1, C23.1, C26.1, R19.1, R23.1, R27.1; also elsewhere on the board
/SIM_2: Q6.1 (B); also elsewhere on the board
/SIM_3: Q8.1 (B); also elsewhere on the board
/SIM_4: Q10.1 (B); also elsewhere on the board
/Simisters/Simister2/AC_IN: Q5.2 (A2), R17.1, R18.2; also elsewhere on the board
/Simisters/Simister2/AC_OUT: C21.2, C22.2, Q5.1 (A1); also elsewhere on the board
/Simisters/Simister3/AC_IN: Q7.2 (A2), R21.1, R22.2; also elsewhere on the board
/Simisters/Simister3/AC_OUT: C24.2, C25.2, Q7.1 (A1); also elsewhere on the board
/Simisters/Simister4/AC_IN: Q9.2 (A2), R25.1, R26.2; also elsewhere on the board
/Simisters/Simister4/AC_OUT: C27.2, C28.2, Q9.1 (A1); also elsewhere on the board
GNDD: C20.2, C23.2, C26.2, Q6.2 (E), Q8.2 (E), Q10.2 (E); also elsewhere on the board
unnamed: C21.1, R18.1
unnamed: C22.1, R16.1, R17.2
unnamed: C24.1, R22.1
unnamed: C25.1, R20.1, R21.2
unnamed: C27.1, R26.1
unnamed: C28.1, R24.1, R25.2
unnamed: OC3.1, R19.2
unnamed: OC3.6, R16.2
unnamed: OC4.1, R23.2
unnamed: OC4.6, R20.2
unnamed: OC5.1, R27.2
unnamed: OC5.6, R24.2
unnamed: OC3.4, Q5.3 (G)
unnamed: OC3.2, Q6.3 (C), TP13.1
unnamed: OC4.4, Q7.3 (G)
unnamed: OC4.2, Q8.3 (C), TP15.1
unnamed: OC5.4, Q9.3 (G)
unnamed: OC5.2, Q10.3 (C), TP17.1
